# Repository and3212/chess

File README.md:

# chess
Chess code for my self playing chess board

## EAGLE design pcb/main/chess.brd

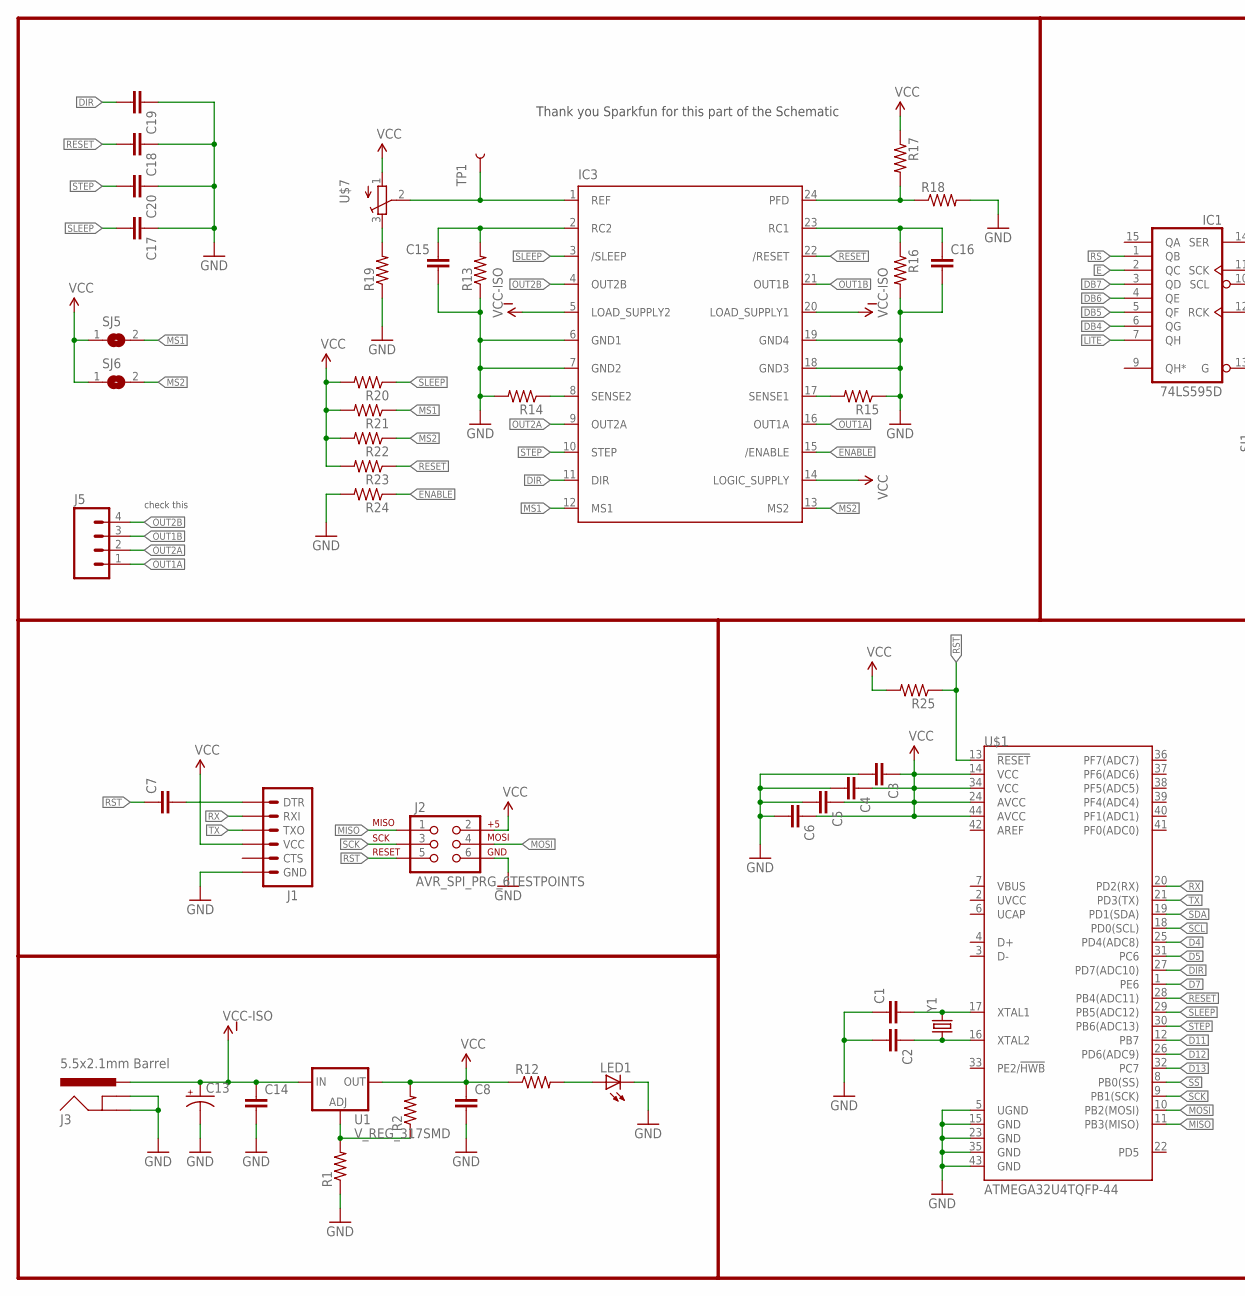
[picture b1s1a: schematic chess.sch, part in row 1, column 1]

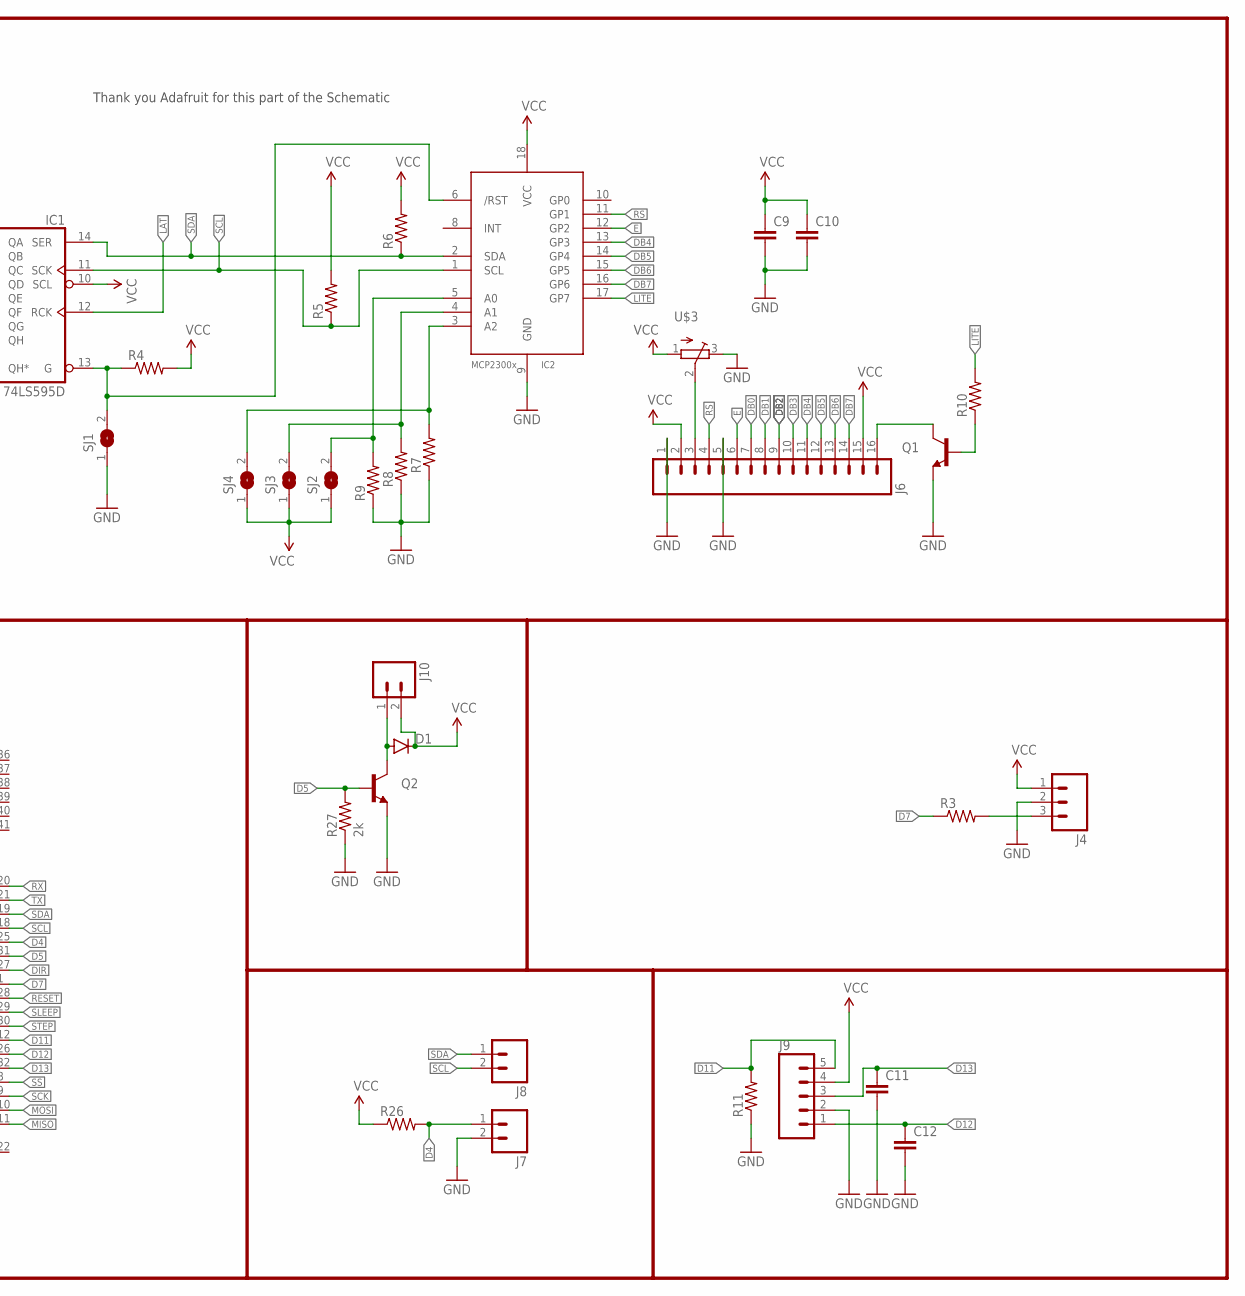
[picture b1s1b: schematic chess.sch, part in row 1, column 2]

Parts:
C1, C2, C3, C4, C5, C6, C7, C8, C9, C10, C11, C12, C14, C15, C16, C17, C18, C19, C20: CAP0603-CAP; 0603-CAP
C13: CAP_POL6032; EIA6032
D1: DIODEBAS16; SOD-323
IC1: 74LS595D; SO16
IC2: MCP2300X/SO; SO18W
IC3: A3967SLB; SO24W
J1: ARDUINO_SERIAL_PROGRAMPTH; 1X06
J2: AVR_SPI_PRG_6TESTPOINTS; 2X3_TEST_POINTS
J3: 5.5x2.1mm Barrel; POWER_JACK_SMD
J4: M03PTH; 1X03
J5: M04PTH; 1X04
J6: M16PTH; 1X16
J7, J8, J10: M02PTH; 1X02
J9: M05PTH; 1X05
LED1: LED1206; LED-1206
Q1: TRANSISTOR_NPNMMBT2222A; SOT23-3
Q2: TRANSISTOR_NPNTO-92-AMMO; TO-92-AMMO
R1, R2, R3, R4, R5, R6, R7, R8, R9, R10, R11, R12, R13, R14, R15, R16, R17, R18, R19, R20, R21, R22, R23, R24, R25, R26: RESISTOR0603-RES; 0603-RES
R27: 2k; 0603-RES
SJ1, SJ2, SJ3, SJ4, SJ5, SJ6: SJ
TP1: TEST-POINT3X5; PAD.03X.05
U1: V_REG_317SMD; SOT223
U$1: ATMEGA32U4TQFP-44; TQFP44
U$3, U$7: TRIMPOTTC33X; TC33X
Y1: CRYSTALCRYSTAL-SMD-5X3-12MHZ; CRYSTAL-SMD-5X3

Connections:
D4: J7.1, R26.2, U$1.25 (PD4(ADC8))
D5: Q2.2 (B), R27.2, U$1.31 (PC6)
D7: R3.1, U$1.1 (PE6)
D11: J9.5, R11.2, U$1.12 (PB7)
D12: C12.1, J9.1, U$1.26 (PD6(ADC9))
D13: C11.1, J9.3, U$1.32 (PC7)
DB0: J6.7
DB1: J6.8
DB2: J6.9
DB3: J6.10
DB4: IC1.6 (QG), IC2.13 (GP3), J6.11
DB5: IC1.5 (QF), IC2.14 (GP4), J6.12
DB6: IC1.4 (QE), IC2.15 (GP5), J6.13
DB7: IC1.3 (QD), IC2.16 (GP6), J6.14
DIR: C19.2, IC3.11 (DIR), U$1.27 (PD7(ADC10))
E: IC1.2 (QC), IC2.12 (GP2), J6.6
ENABLE: IC3.15 (/ENABLE), R24.1
GND: C1.1, C2.2, C3.2, C4.2, C5.2, C6.2, C8.2, C9.2, C10.2, C11.2, C12.2, C13.P$2 (-), C14.2, C15.2, C16.2, C17.1, C18.1, C19.1, C20.1, IC1.8 (GND), IC2.9 (GND), IC3.6 (GND1), IC3.7 (GND2), IC3.18 (GND3), IC3.19 (GND4), J1.6 (GND), J2.6, J3.GND (GNDBREAK), J3.P$4 (GND), J4.2, J6.1, J6.5, J7.2, J9.2, LED1.C, Q1.2 (E), Q2.1 (E), R1.1, R7.1, R8.1, R9.1, R11.1, R13.1, R14.2, R15.1, R16.2, R18.2, R19.1, R24.2, R27.1, SJ1.1, U$1.5 (UGND), U$1.15 (GND), U$1.23 (GND), U$1.35 (GND), U$1.43 (GND), U$3.3 (E)
LAT: IC1.12 (RCK)
LITE: IC1.7 (QH), IC2.17 (GP7), R10.2
MISO: J2.1, U$1.11 (PB3(MISO))
MOSI: J2.4, U$1.10 (PB2(MOSI))
MS1: IC3.12 (MS1), R21.1, SJ5.2
MS2: IC3.13 (MS2), R22.1, SJ6.2
unnamed: C7.2, J1.1 (DTR)
unnamed: R1.2, R2.1, U1.1 (ADJ)
unnamed: D1.A, J10.1, Q2.3 (C)
unnamed: IC3.8 (SENSE2), R14.1
unnamed: J4.3, R3.2
unnamed: C2.1, U$1.16 (XTAL2), Y1.1
unnamed: C1.2, U$1.17 (XTAL1), Y1.3 (2)
unnamed: LED1.A, R12.2
unnamed: IC3.1 (REF), TP1.P$1, U$7.2 (S)
unnamed: R19.2, U$7.3 (E)
unnamed: IC1.13 (G), IC2.6 (/RST), R4.1, SJ1.2
unnamed: J6.3, U$3.2 (S)
unnamed: Q1.1 (B), R10.1
unnamed: C15.1, IC3.2 (RC2), R13.2
unnamed: J6.16, Q1.3 (C)
unnamed: IC2.5 (A0), R9.2, SJ2.2
unnamed: IC2.4 (A1), R8.2, SJ3.2
unnamed: IC2.3 (A2), R7.2, SJ4.2
unnamed: IC3.17 (SENSE1), R15.2
unnamed: C16.1, IC3.23 (RC1), R16.1
unnamed: IC3.24 (PFD), R17.2, R18.1
OUT1A: IC3.16 (OUT1A), J5.1
OUT1B: IC3.21 (OUT1B), J5.3
OUT2A: IC3.9 (OUT2A), J5.2
OUT2B: IC3.4 (OUT2B), J5.4
RESET: C18.2, IC3.22 (/RESET), R23.1, U$1.28 (PB4(ADC11))
RS: IC1.1 (QB), IC2.11 (GP1), J6.4
RST: C7.1, J2.5, R25.1, U$1.13 (!RESET)
RX: J1.2 (RXI), U$1.20 (PD2(RX))
SCK: J2.3, U$1.9 (PB1(SCK))
SCL: IC1.11 (SCK), IC2.1 (SCL), J8.2, R5.1, U$1.18 (PD0(SCL))
SDA: IC1.14 (SER), IC2.2 (SDA), J8.1, R6.1, U$1.19 (PD1(SDA))
SLEEP: C17.2, IC3.3 (/SLEEP), R20.1, U$1.29 (PB5(ADC12))
SS: U$1.8 (PB0(SS))
STEP: C20.2, IC3.10 (STEP), U$1.30 (PB6(ADC13))
TX: J1.3 (TXO), U$1.21 (PD3(TX))
VCC: C3.1, C4.1, C5.1, C6.1, C8.1, C9.1, C10.1, D1.C, IC1.10 (SCL), IC1.16 (VCC), IC2.18 (VCC), IC3.14 (LOGIC_SUPPLY), J1.4 (VCC), J2.2, J4.1, J6.2, J6.15, J9.4, J10.2, R2.2, R4.2, R5.2, R6.2, R12.1, R17.1, R20.2, R21.2, R22.2, R23.2, R25.2, R26.1, SJ2.1, SJ3.1, SJ4.1, SJ5.1, SJ6.1, U1.2 (OUT), U$1.14 (VCC), U$1.24 (AVCC), U$1.34 (VCC), U$1.44 (AVCC), U$3.1 (A), U$7.1 (A)
VCC-ISO: C13.P$1 (+), C14.1, IC3.5 (LOAD_SUPPLY2), IC3.20 (LOAD_SUPPLY1), J3.VIN0 (PWR), U1.3 (IN)

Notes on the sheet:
Thank you Adafruit for this part of the Schematic
Thank you Sparkfun for this part of the Schematic
check this

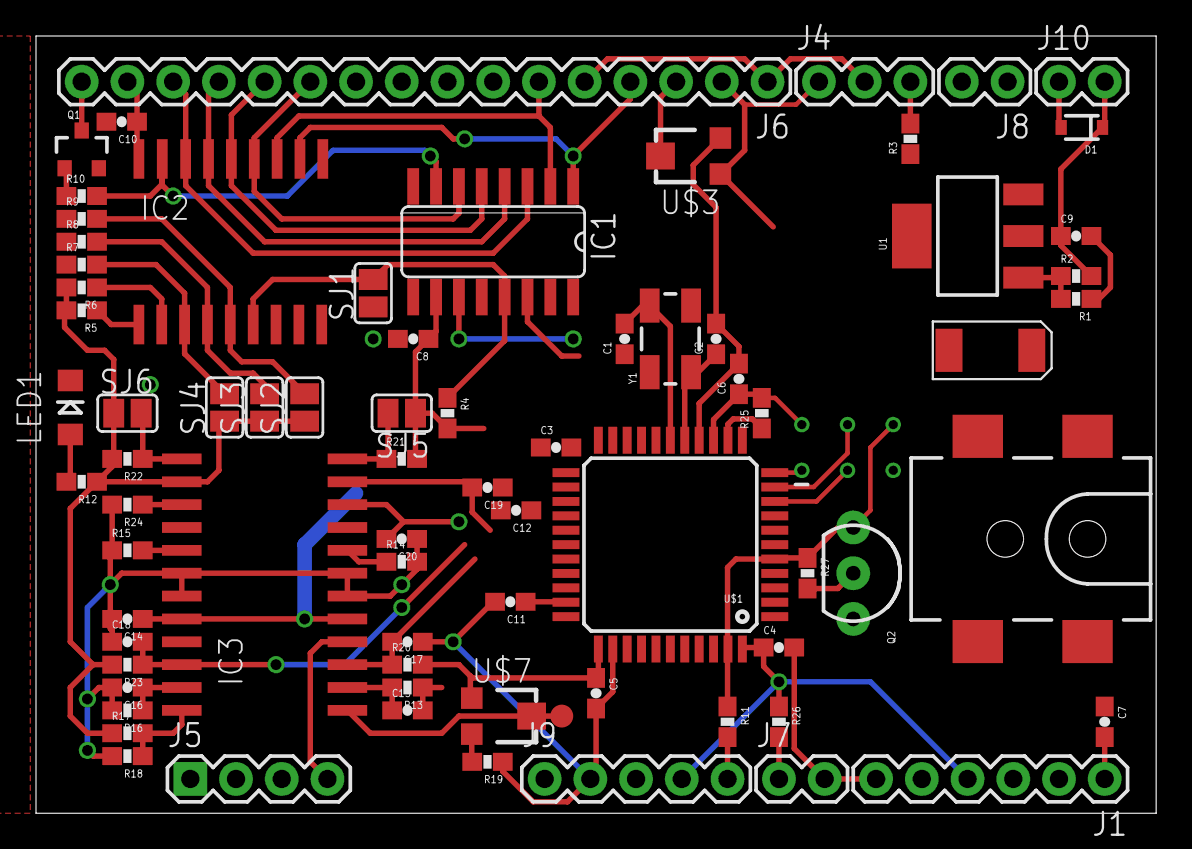
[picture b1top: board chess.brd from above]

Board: 2 copper layers, 62.2 x 43.2 mm, 76 parts (0 on the bottom side), 56 nets.

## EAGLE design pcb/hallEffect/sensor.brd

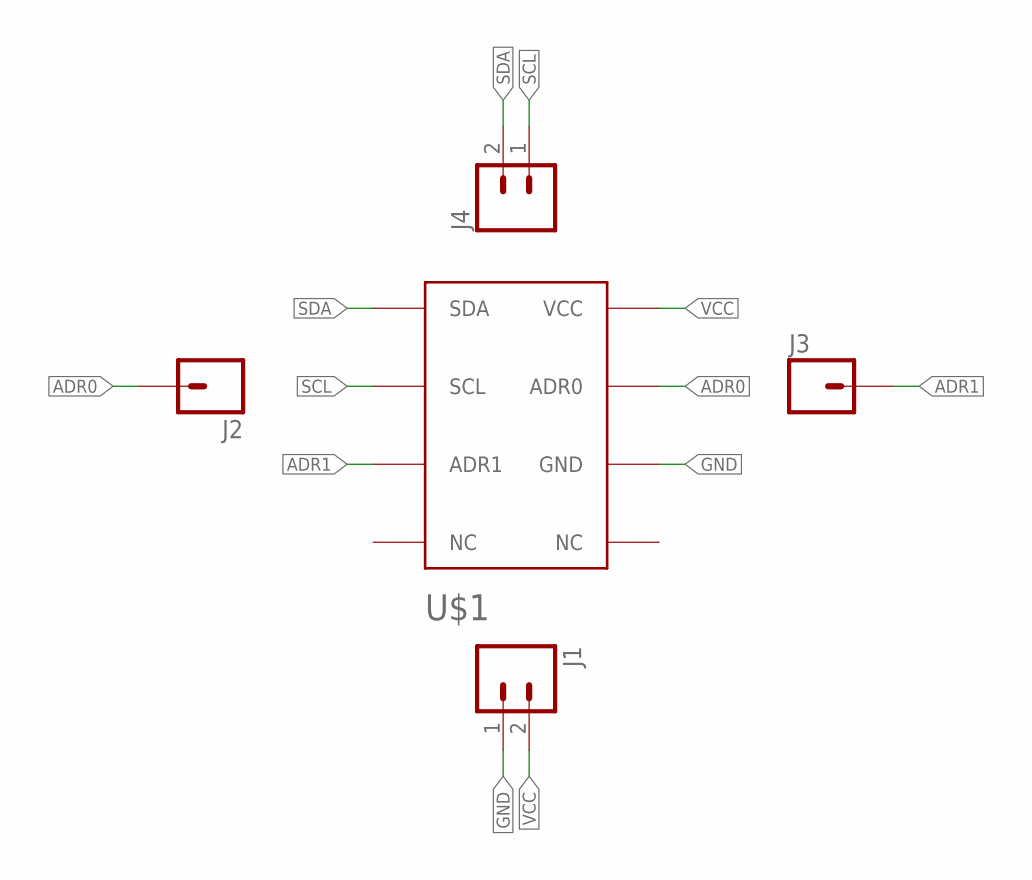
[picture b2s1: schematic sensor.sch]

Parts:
J1, J4: M02PTH; 1X02
J2, J3: M01PTH; 1X01
U$1: A1454; TSSOP8

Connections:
ADR0: J2.1, U$1.2 (ADR0)
ADR1: J3.1, U$1.6 (ADR1)
GND: J1.1, U$1.3 (GND)
SCL: J4.1, U$1.8 (SCL)
SDA: J4.2, U$1.7 (SDA)
VCC: J1.2, U$1.1 (VCC)

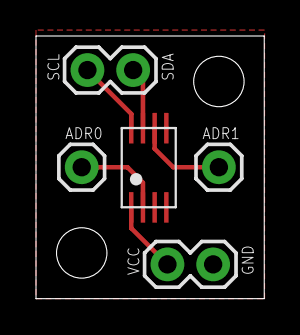
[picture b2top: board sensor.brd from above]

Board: 2 copper layers, 12.7 x 14.6 mm, 5 parts (0 on the bottom side), 6 nets.

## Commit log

2017-01-02 Almost finished workin on the pawn
2017-01-02 Rook is a bit buggy and can take its own pieces (somtimes), need to fix that
2017-01-02 Updated comments and added bishop, still need to fix rook problem
2017-01-03 added a .gitattributes to hopefully remove the eagle file from the percentage bar
2017-01-03 trying to fix .gitattributes
2017-01-03 added some folders, trying to fix gitattributes
2017-01-03 Hopefully got gitattributes fixed
2017-01-03 Finished knight code, rook and bishop still broken
2017-01-03 Added a coordinate system so you now input a set such as 'e' and then 4
2017-01-03 Added PCB files
    Files for the hall effect sensor and main board added
2017-01-03 Fixed coordinate system
2017-01-03 Last commit of the night
2017-01-03 Changed the methods for all of the pieces, now they reference board[ ][ ] instead of just being passed it
2017-01-03 Update pieces.cpp
    Fixed moves list to reset and stop the ability to capture one's own pieces
2017-01-03 Update pieces.cpp
    Fixed reset loop for pi
2017-01-04 Update pieces.cpp
    Attempted to fix bishop. Added breaks to loops so it didn't calculate pieces off the board but still not fully operational
2017-01-04 Update pieces.cpp
    Fixed the bishop
2017-01-04 Update pieces.cpp
    Fixed Knight movement
2017-01-04 Update pieces.cpp
    Added King and Queen + resetList method
2017-01-04 Update main.cpp
    Added King and Queen
2017-01-04 Update pieces.hpp
    Added King and Queen
2017-01-04 Update main.cpp
    made turn sequence so white and black must move in order. Added isInCheck method, which is not fully operational yet but not detrimental to current program performance
2017-01-04 Update main.cpp
    check method works on all but some diagonals
2017-01-06 Update main.cpp
    Fixed check to work with pawns and knights
2017-01-06 Update main.cpp
    Prevents illegal moves
2017-05-11 Started the rework to make it work with AVRs
2017-05-12 Added I2C functions to watchDog.c
2017-05-29 Changed code from C to Arduino for simplicity, we can switch back to Avr-C later

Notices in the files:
parts and their libraries:
SparkFun-Connectors: Licensing: Creative Commons ShareAlike 4.0 International - https://creativecommons.org/licenses/by-sa/4.0
